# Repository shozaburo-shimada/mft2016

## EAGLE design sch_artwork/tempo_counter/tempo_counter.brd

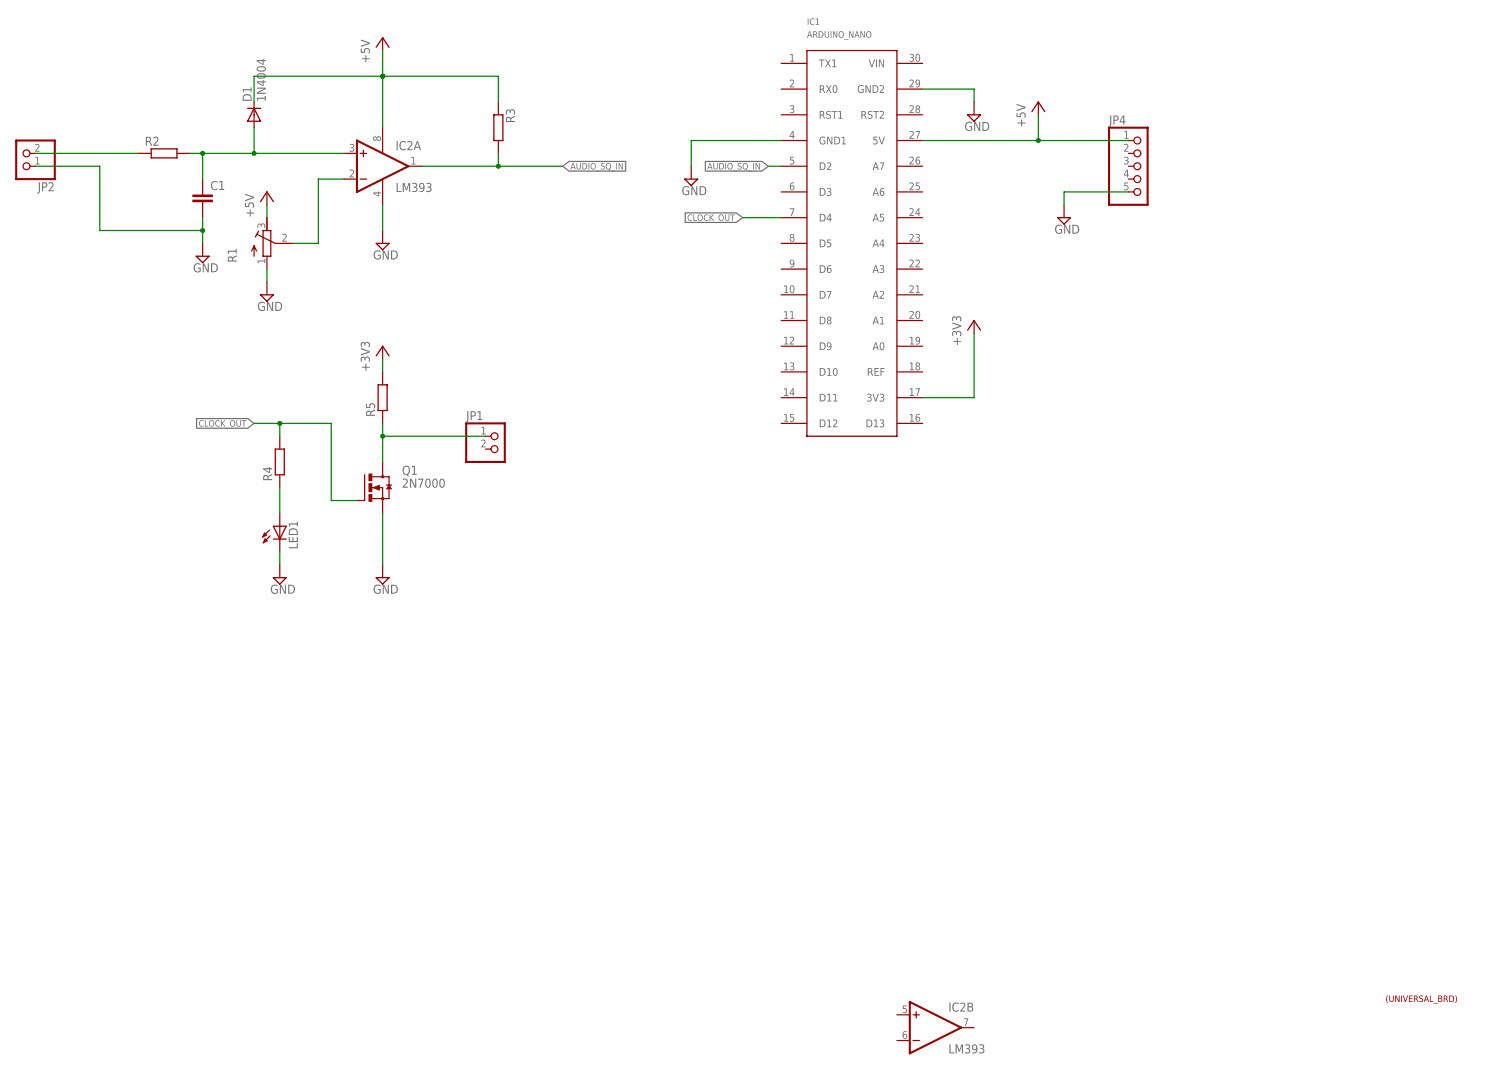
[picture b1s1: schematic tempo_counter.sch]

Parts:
C1: C_DIP_2.54_1; C_DIP2.54_1
D1: 1N4004; DO41-10
IC1: ARDUINO_NANO
IC2: LM393; DIL08_UNIV
JP1, JP2: PINHD-1X2; 1X02
JP4: PINHD-1X5; 1X05
LED1: LED_ELD260; LED_LD260
Q1: 2N7000; TO92
R1: R-TRIMM64W; RTRIM64W
R2, R3, R4, R5: R_DIP_4; R_DIP2.54_4
U$1: UNIVERSAL_BRD_72MM_47MM; UNIVERSAL_BRD_72MM_47MM_SMALL

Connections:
+3V3: IC1.17 (3V3), R5.2
+5V: D1.C, IC1.27 (5V), IC2.8 (V+), JP4.1, R1.3 (E), R3.1
AUDIO_SQ_IN: IC1.5 (D2), IC2.1 (OUT), R3.2
CLOCK_OUT: IC1.7 (D4), Q1.G, R4.2
GND: C1.2, IC1.4 (GND1), IC1.29 (GND2), IC2.4 (V-), JP2.1, JP4.5, LED1.K (C), Q1.S, R1.1 (A)
unnamed: JP2.2, R2.1
unnamed: LED1.A, R4.1
unnamed: IC2.2 (-IN), R1.2 (S)
unnamed: C1.1, D1.A, IC2.3 (+IN), R2.2
unnamed: JP1.1, Q1.D, R5.1

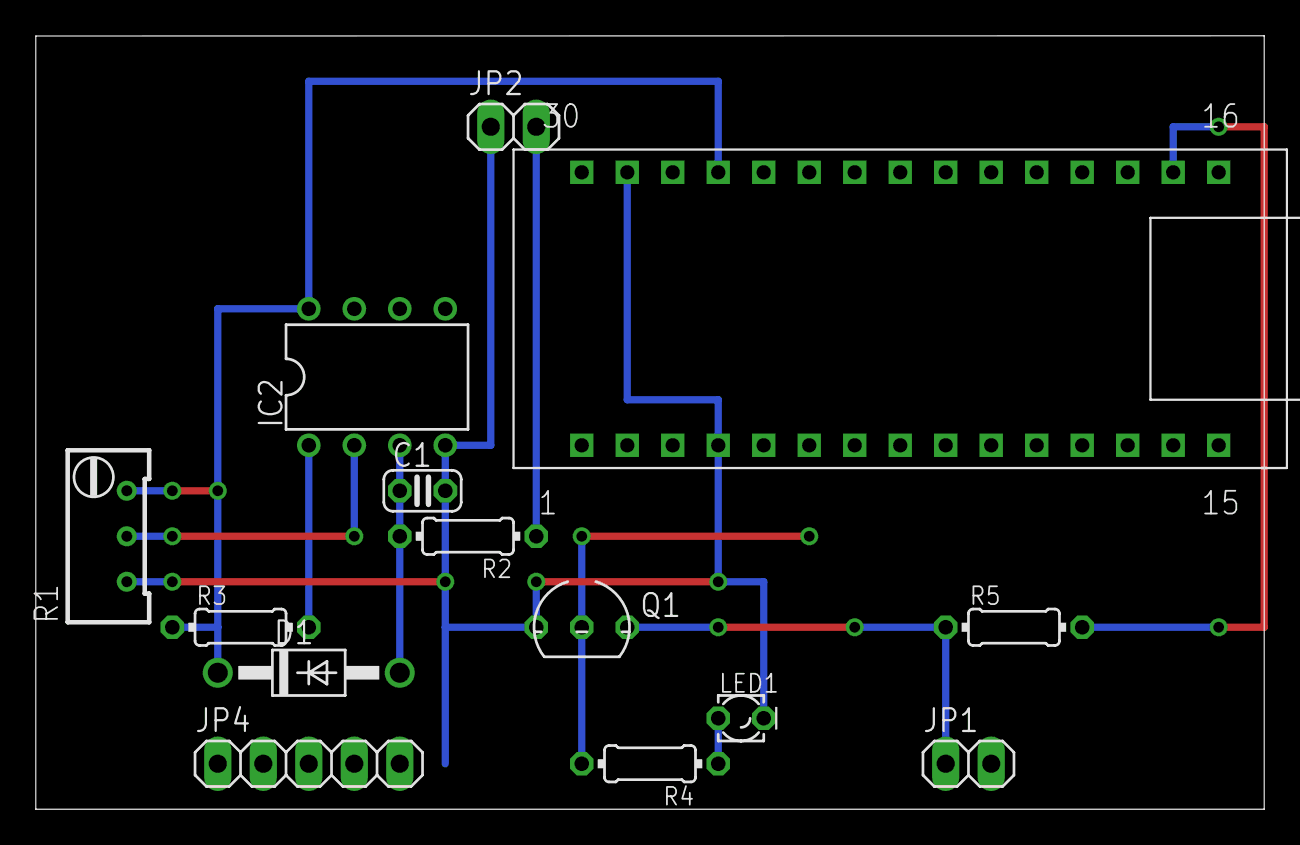
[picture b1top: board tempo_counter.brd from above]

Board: 2 copper layers, 68.6 x 43.2 mm, 15 parts (0 on the bottom side), 10 nets.

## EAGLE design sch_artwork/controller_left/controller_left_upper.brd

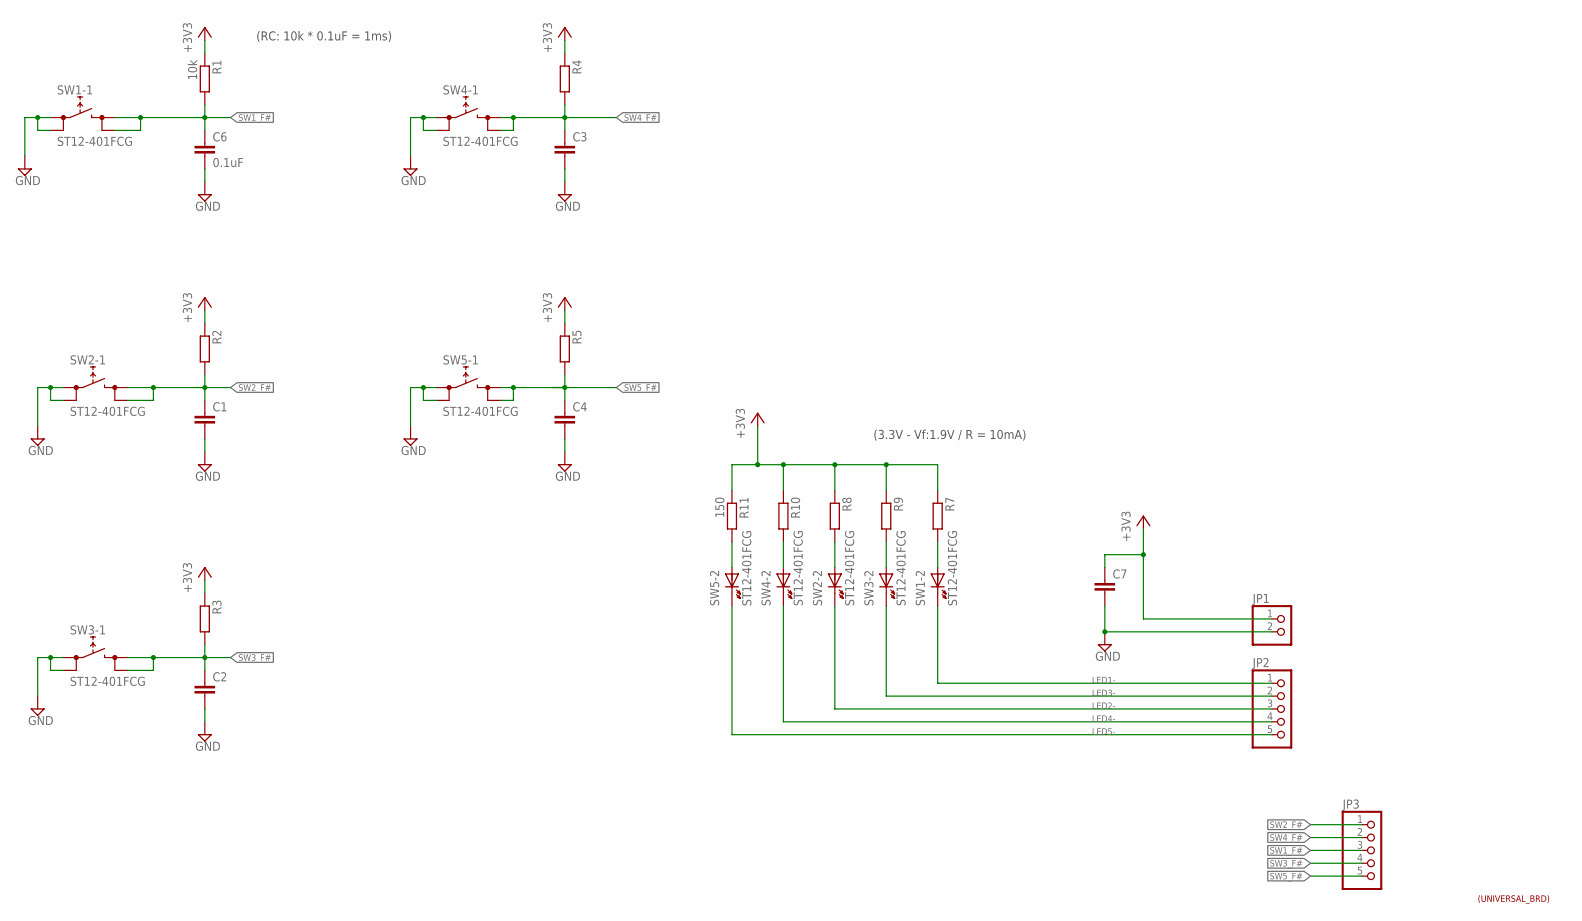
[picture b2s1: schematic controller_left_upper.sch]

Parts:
C1, C2, C3, C4, C7: C_DIP_2.54_1; C_DIP2.54_1
C6: 0.1uF; C_DIP2.54_1
JP1: PINHD-1X2; 1X02
JP2, JP3: PINHD-1X5; 1X05
R1: 10k; R_DIP2.54_4
R2, R3, R4, R5, R7, R8, R9, R10: R_DIP_4; R_DIP2.54_4
R11: 150; R_DIP2.54_4
SW1, SW2, SW3, SW4, SW5: ST12-401FCG
U$1: UNIVERSAL_BRD_95MM_72MM

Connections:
+3V3: C7.1, JP1.1, R1.1, R2.1, R3.1, R4.1, R5.1, R7.1, R8.1, R9.1, R10.1, R11.1
GND: C1.2, C2.2, C3.2, C4.2, C6.2, C7.2, JP1.2, SW1.1 (0), SW1.2 (0), SW2.1 (0), SW2.2 (0), SW3.1 (0), SW3.2 (0), SW4.1 (0), SW4.2 (0), SW5.1 (0), SW5.2 (0)
LED1-: JP2.1, SW1.- (K)
LED2-: JP2.3, SW2.- (K)
LED3-: JP2.2, SW3.- (K)
LED4-: JP2.4, SW4.- (K)
LED5-: JP2.5, SW5.- (K)
unnamed: R9.2, SW3.+ (A)
unnamed: R8.2, SW2.+ (A)
unnamed: R10.2, SW4.+ (A)
unnamed: R11.2, SW5.+ (A)
unnamed: R7.2, SW1.+ (A)
SW1_F#: C6.1, JP3.3, R1.2, SW1.3 (1), SW1.4 (1)
SW2_F#: C1.1, JP3.1, R2.2, SW2.3 (1), SW2.4 (1)
SW3_F#: C2.1, JP3.4, R3.2, SW3.3 (1), SW3.4 (1)
SW4_F#: C3.1, JP3.2, R4.2, SW4.3 (1), SW4.4 (1)
SW5_F#: C4.1, JP3.5, R5.2, SW5.3 (1), SW5.4 (1)

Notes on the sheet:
(RC: 10k * 0.1uF = 1ms)
(3.3V - Vf:1.9V / R = 10mA)

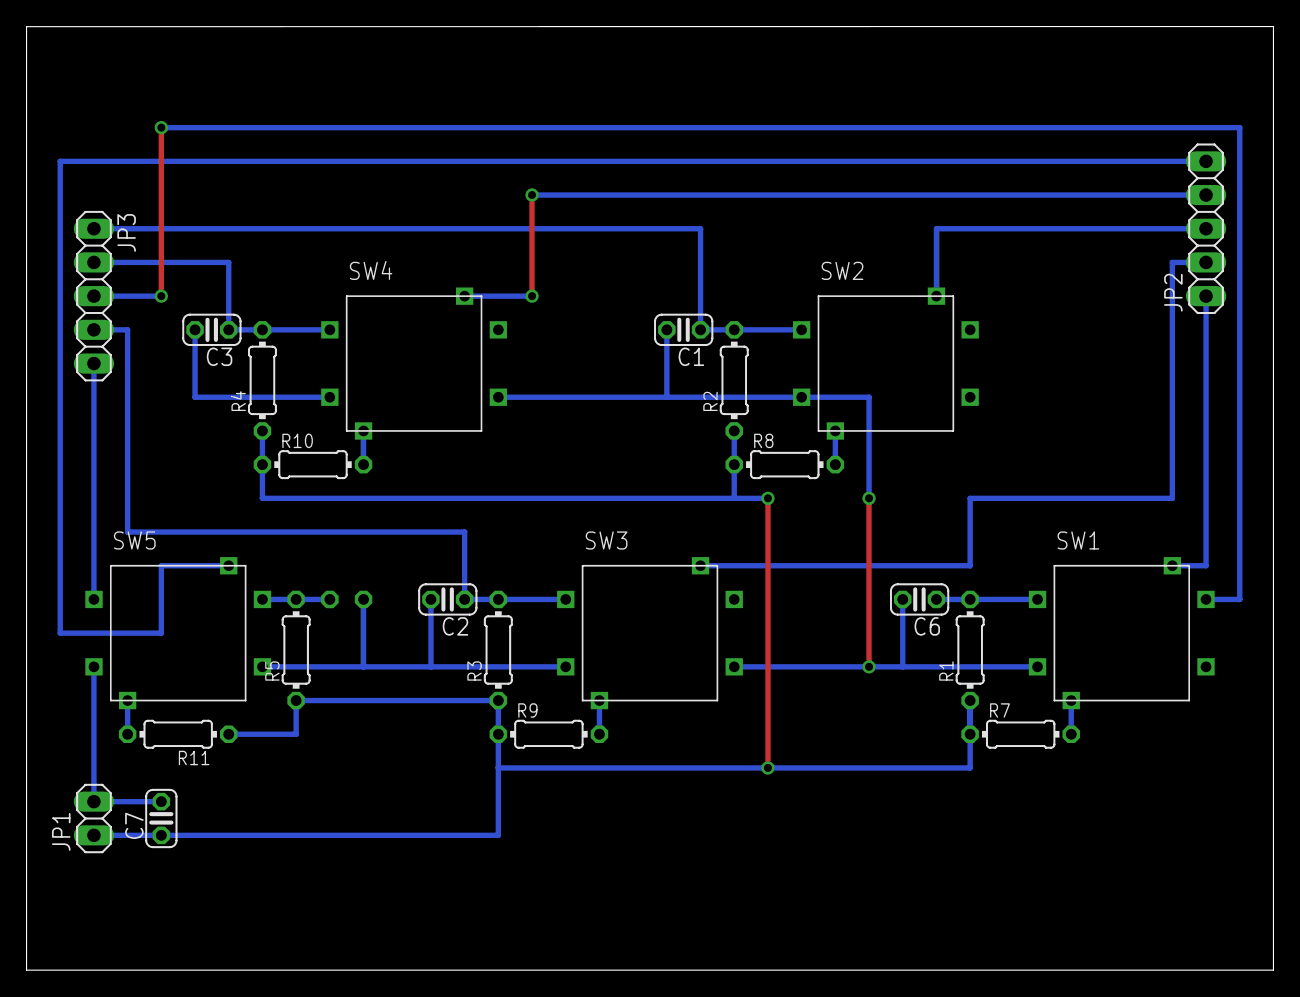
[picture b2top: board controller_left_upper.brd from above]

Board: 2 copper layers, 94.0 x 71.1 mm, 25 parts (1 on the bottom side), 17 nets.

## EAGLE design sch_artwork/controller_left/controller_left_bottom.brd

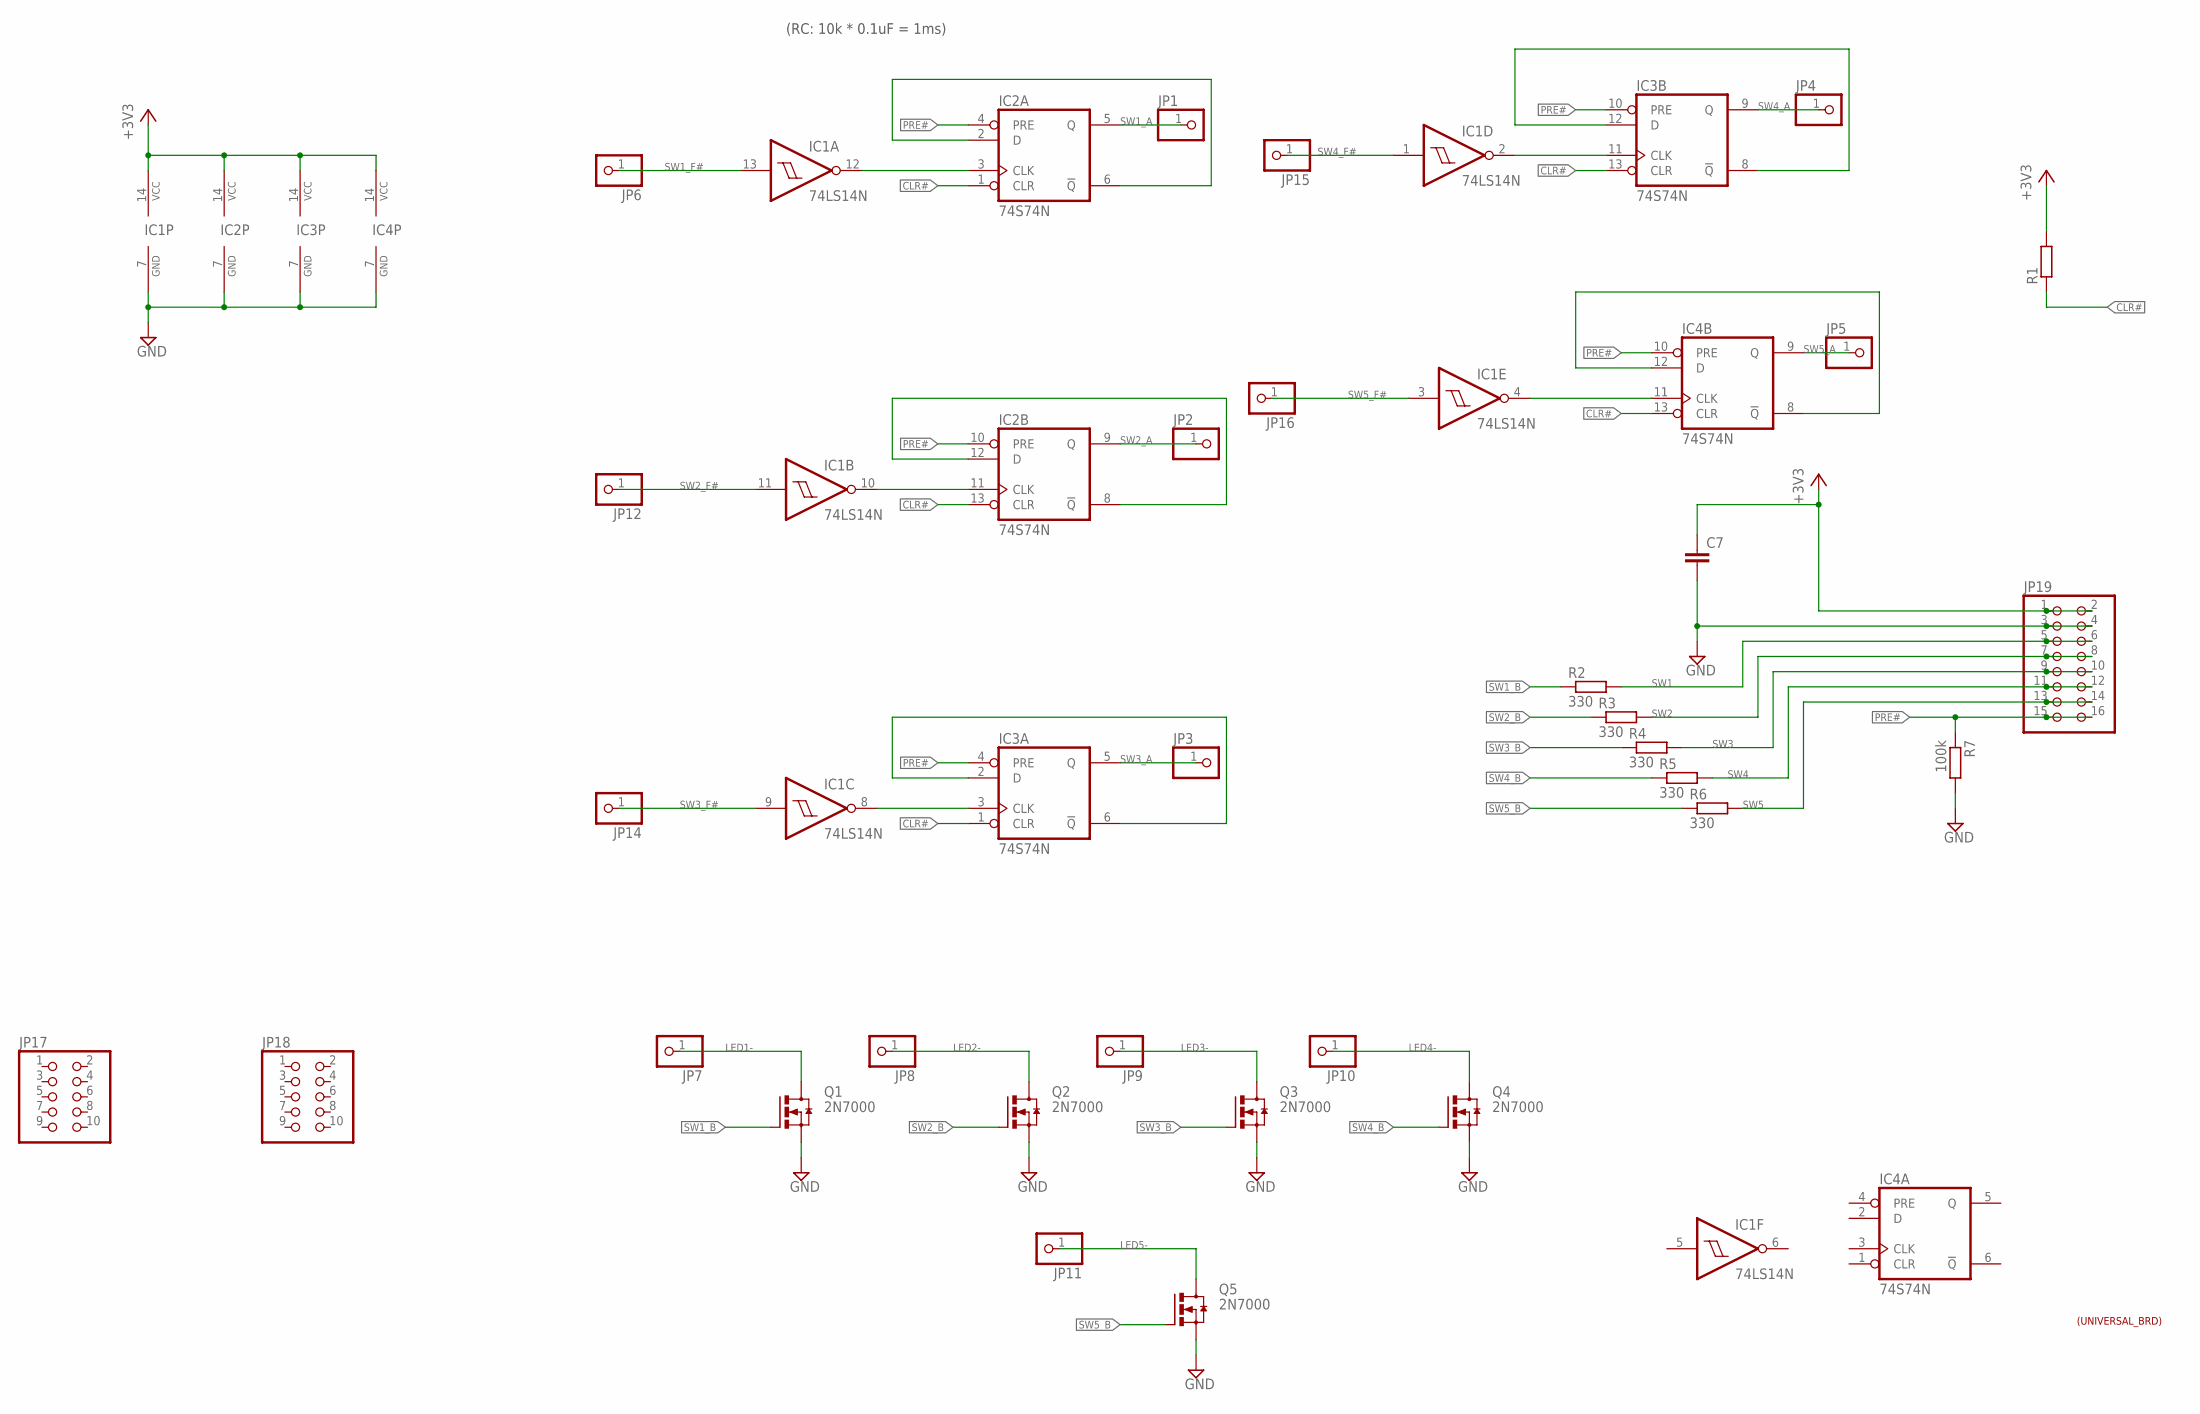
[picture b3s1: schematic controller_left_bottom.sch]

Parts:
C7: C_DIP_2.54_1; C_DIP2.54_1
IC1: 74LS14N; DIL14
IC2, IC3, IC4: 74S74N; DIL14
JP1, JP2, JP3, JP4, JP5, JP6, JP7, JP8, JP9, JP10, JP11, JP12, JP14, JP15, JP16: PINHD-1X1; 1X01_UNIVERSAL_BRD
JP17, JP18: PINHD-2X5; 2X05
JP19: PINHD-2X8; 2X08
Q1, Q2, Q3, Q4, Q5: 2N7000; TO92
R1: R_DIP_4; R_DIP2.54_4
R2, R3, R4, R5, R6: 330; R_DIP2.54_4
R7: 100k; R_DIP2.54_4
U$1: UNIVERSAL_BRD_95MM_72MM

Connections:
+3V3: C7.1, IC1.14 (VCC), IC2.14 (VCC), IC3.14 (VCC), IC4.14 (VCC), JP19.1, JP19.2, R1.2
CLR#: IC2.1 (CLR), IC2.13 (CLR), IC3.1 (CLR), IC3.13 (CLR), IC4.13 (CLR), R1.1
GND: C7.2, IC1.7 (GND), IC2.7 (GND), IC3.7 (GND), IC4.7 (GND), JP19.3, JP19.4, Q1.S, Q2.S, Q3.S, Q4.S, Q5.S, R7.2
LED1-: JP7.1, Q1.D
LED2-: JP8.1, Q2.D
LED3-: JP9.1, Q3.D
LED4-: JP10.1, Q4.D
LED5-: JP11.1, Q5.D
unnamed: IC2.2 (D), IC2.6 (!Q)
unnamed: IC4.8 (!Q), IC4.12 (D)
unnamed: IC3.2 (D), IC3.6 (!Q)
unnamed: IC1.4 (O), IC4.11 (CLK)
unnamed: IC2.8 (!Q), IC2.12 (D)
unnamed: IC1.12 (O), IC2.3 (CLK)
unnamed: IC1.10 (O), IC2.11 (CLK)
unnamed: IC1.8 (O), IC3.3 (CLK)
unnamed: IC3.8 (!Q), IC3.12 (D)
unnamed: IC1.2 (O), IC3.11 (CLK)
PRE#: IC2.4 (PRE), IC2.10 (PRE), IC3.4 (PRE), IC3.10 (PRE), IC4.10 (PRE), JP19.15, JP19.16, R7.1
SW1: JP19.5, JP19.6, R2.2
SW1_A: IC2.5 (Q), JP1.1
SW1_B: Q1.G, R2.1
SW1_F#: IC1.13 (I), JP6.1
SW2: JP19.7, JP19.8, R3.2
SW2_A: IC2.9 (Q), JP2.1
SW2_B: Q2.G, R3.1
SW2_F#: IC1.11 (I), JP12.1
SW3: JP19.9, JP19.10, R4.2
SW3_A: IC3.5 (Q), JP3.1
SW3_B: Q3.G, R4.1
SW3_F#: IC1.9 (I), JP14.1
SW4: JP19.11, JP19.12, R5.2
SW4_A: IC3.9 (Q), JP4.1
SW4_B: Q4.G, R5.1
SW4_F#: IC1.1 (I), JP15.1
SW5: JP19.13, JP19.14, R6.2
SW5_A: IC4.9 (Q), JP5.1
SW5_B: Q5.G, R6.1
SW5_F#: IC1.3 (I), JP16.1

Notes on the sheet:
(RC: 10k * 0.1uF = 1ms)

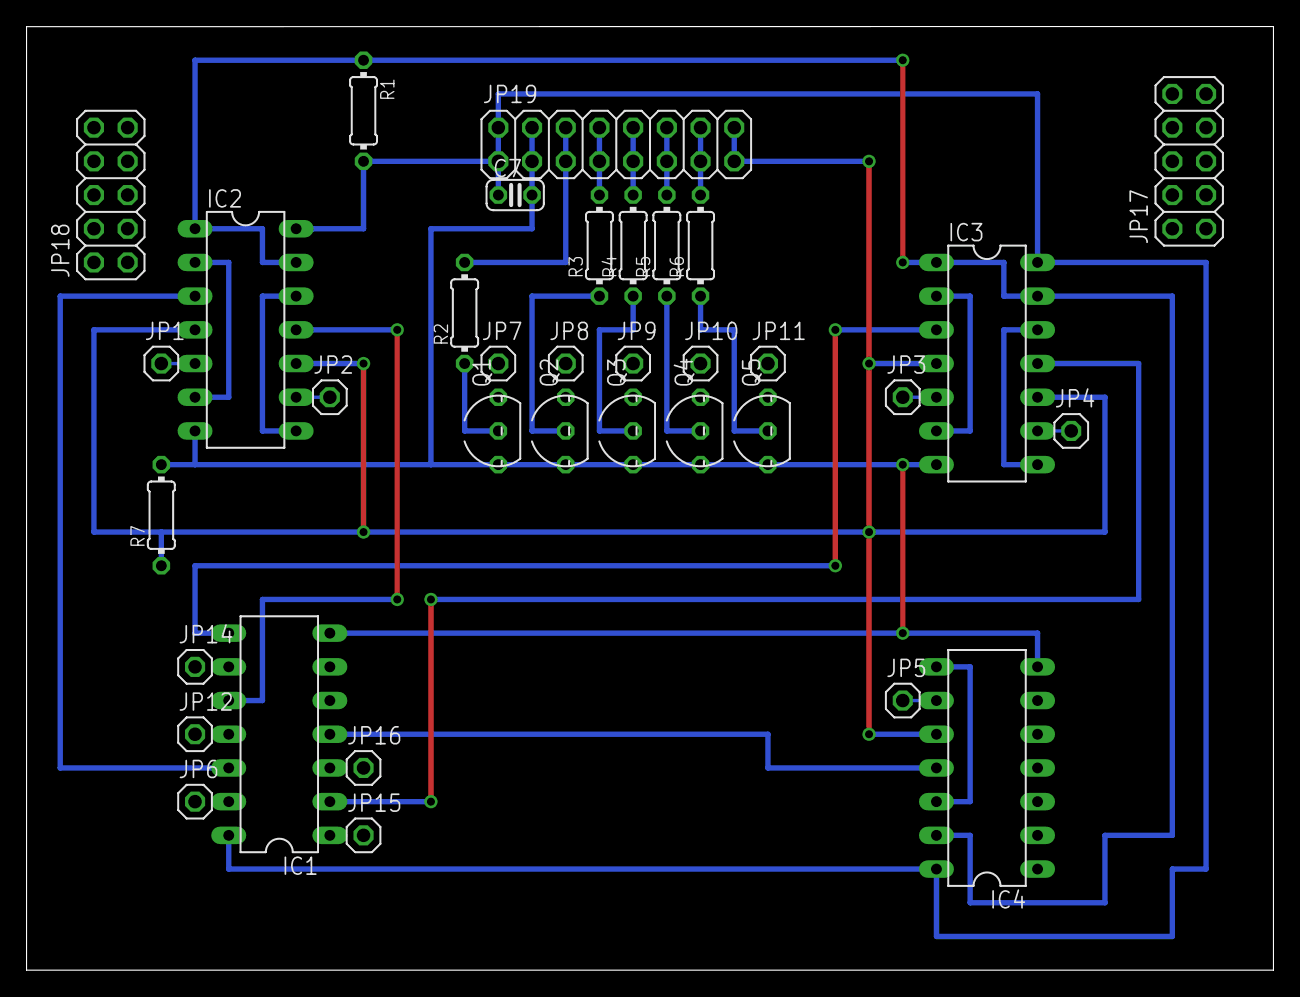
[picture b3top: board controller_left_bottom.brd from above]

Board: 2 copper layers, 94.0 x 71.1 mm, 36 parts (0 on the bottom side), 39 nets.
